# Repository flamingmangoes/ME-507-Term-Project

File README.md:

This project is a 1 rotational degree of freedom prototype for an autonomously controlled momentum exchange device. It includes a reaction flywheel driven by a brushless DC motor, a printed circuit board schematic and layout for the motor controller, and a software architecture to interact with the ESP32 microcontroller.

The hardware consists of a reaction flywheel, its housing, the brushless DC motor, a frictionless air spindle, a test stand, an air compressor, and the PCB with its necessary components. More information can be found in the README.md in the hardware folder: (https://github.com/flamingmangoes/ME-507-Term-Project/blob/main/hardware/README.md)

The software relies on a FreeRTOS-based task architecture, and it has functionality for wireless speed and torque command of the motor, live speed readout, live gain tuning, and downloading a CSV of test data.
The task diagram is as follows: 

The interrupt service handler in the Driver class sends a timestamp to the edge_time queue when it detects a rising edge on the FGOUT pin. The readActual task takes each rising edge and uses the previous rising edge to calculate the electrical frequency of the motor. It then uses that with the direction to calculate the signed speed in RPM, and places that into the speed_actual share. This task runs whenever it detects a value in edge_time, with a latency of 1ms since it uses an ISR.

This share is then read by the webserver task with a period of 10ms, which plots it on a live readout. It is also read by the speedControl task, which then uses the embedded finite state machine (discussed in the next subsection) to decide how to command the motor. It calls the command_speed_PWM method shown earlier to command the motor speed. 

The webserver can command speeds and torques. When a value is input to the form, it places the command in its respective queue. When a speed is commanded, the speedControl task reads it directly. When a torque is commanded, the calcSetpoint task calls the Euler integrator method from the Controller class to convert that into a speed, then sends that to the speedControl task.

The state diagram for the speedControl task is as follows:

The task starts in idle state. Once a value is placed in the speed_cmd queue, the state machine compares the magnitudes and signs of speed_cmd and the current value of speed_actual and decides in what state to place the motor. In the acceleration state, the motor is using its internal control loop to accelerate to the desired speed, then returns to IDLE once it reaches a deadband of 20rpm. In the deceleration state, the BRAKE pin is set to HIGH and the motor decelerates. (Right now, we cannot control the deceleration torque, but we are planning to implement a bang-bang controller to do so). In zero crossing states, once the motor reaches a deadband of 20 rpm around zero, the DIR pin switches polarity and starts accelerating to the desired speed.

When not in IDLE state, the task compares speed_cmd to speed_actual at a period of 10ms. When in IDLE state, the task blocks until another value is placed in the speed_cmd queue. 

Software documentation is included as a Doxygen-generated HTML file structure in the docs folder. The code itself is also well commented and defines all functions, classes, and variables.

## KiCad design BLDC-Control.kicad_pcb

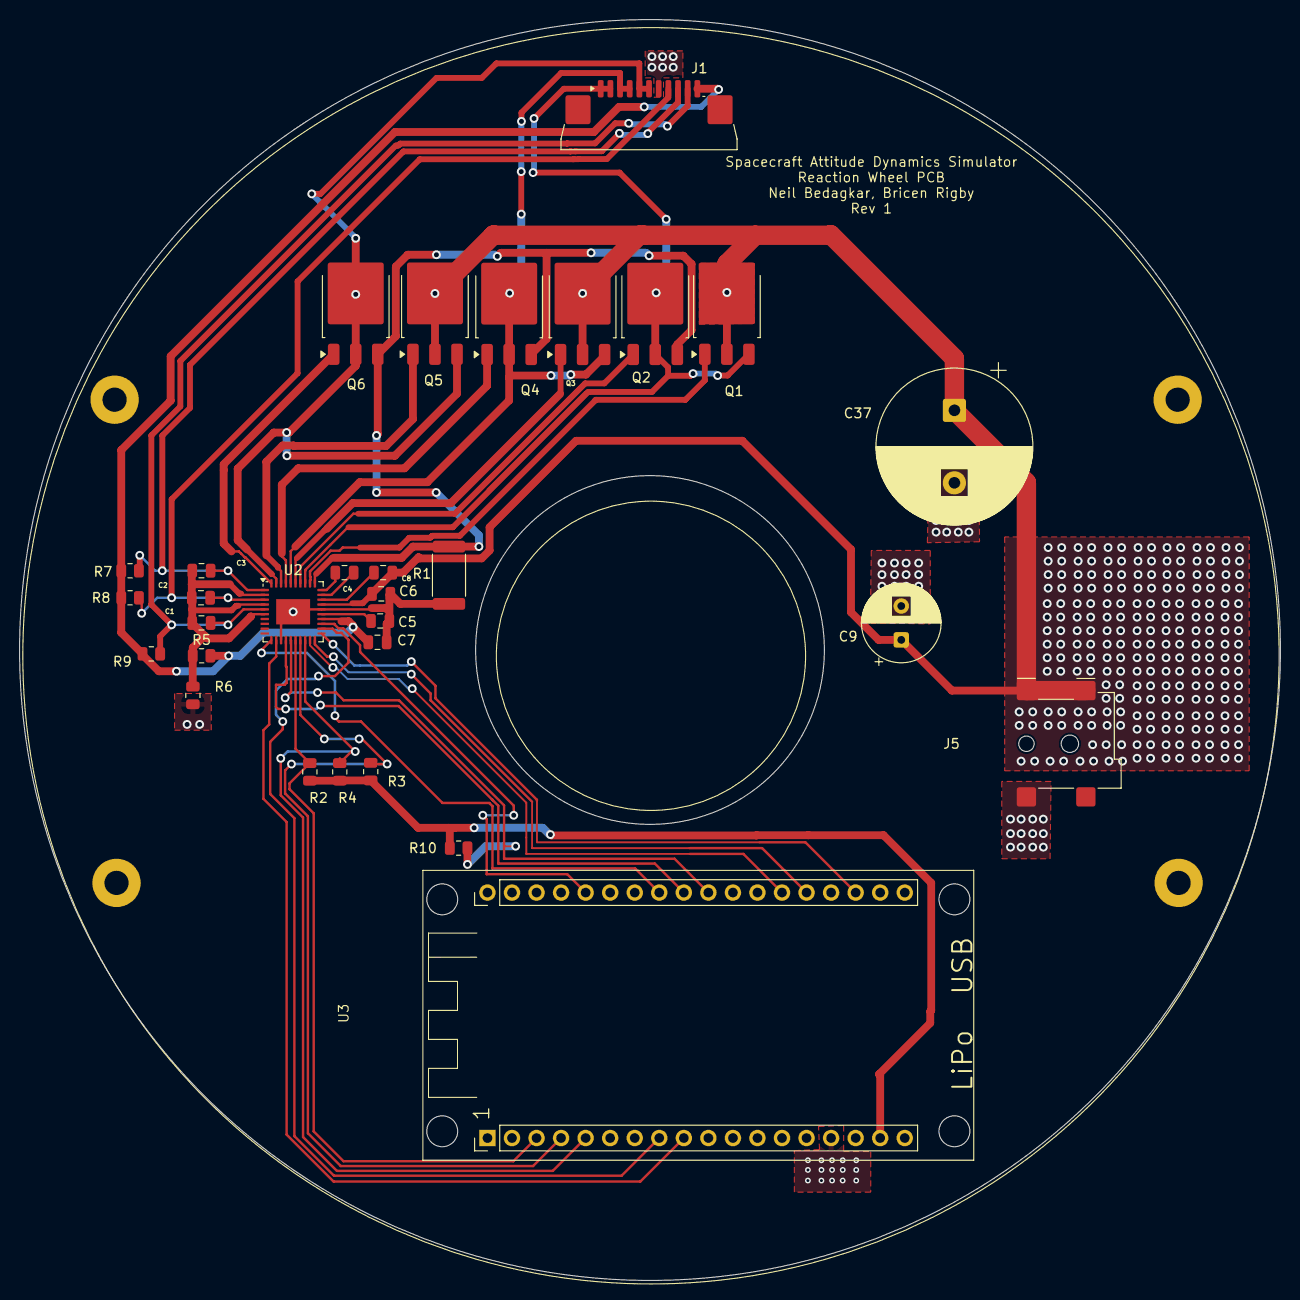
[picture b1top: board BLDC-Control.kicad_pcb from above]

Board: 2 copper layers, 130.5 x 130.5 mm, 34 parts (0 on the bottom side), 34 nets.

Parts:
C1, C2, C3, C4, C6, C7: 0.1 uF; C_0805_2012Metric
C5, C8: 1 uF; C_0805_2012Metric
C9: 47 uF; CP_Radial_D8.0mm_P3.50mm
C37: 470 uF; CP_Radial_D16.0mm_P7.50mm
H1, H2, H3, H4: MountingHole; MountingHole_2.5mm_Pad
J1: BLDC Motor ZIF Connection; JUSHUO_AFA07-S11FCA-00_1x11-1MP_P1.0mm_Horizontal
J5: +24V Power; BarrelJack_Wuerth_694108106102_2.5x5.5mm
Q1, Q2, Q3, Q4, Q5, Q6: Q_NMOS_GDS; TO-252-3_TabPin2
R1: 0.125; R_2512_6332Metric
R2, R3, R4: 10k; R_0805_2012Metric
R5, R6, R7, R8, R9: 2.6k; R_0805_2012Metric
R10: 3.3k; R_0805_2012Metric
U2: DRV8308; Texas_RHA0040E_VQFN-40-1EP_6x6mm_P0.5mm_EP3.52x2.62mm
U3: FireBeetle-ESP32

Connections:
+3V3: R2.2, R3.2, R4.2, R10.1, U3.17 (3V3)
+24V: C6.2, C8.2, C9.1, C37.1, J5.1, Q1.2 (D), Q3.2 (D), Q5.2 (D), U2.27 (VM)
/BRAKE: U2.20 (BRAKE), U3.23 (MCLK/IO12)
/CLKIN: U2.19 (CLKIN), U3.24 (BCLK/IO14)
/DIR: U2.21 (DIR), U3.21 (DI/IO16)
/ENABLE: U2.22 (ENABLE), U3.8 (IO13)
/IOFAULTn_1: R3.1, U2.17 (~FAULTn), U3.4 (IO26)
/IOFGOUT_1: R2.1, U2.16 (FGOUT), U3.3 (IO25)
/IOLOCKn_1: R4.1, U2.18 (~LOCKn), U3.5 (IO27)
/RESET: U2.23 (RESET), U3.32 (IO15)
/SCLK: U2.11 (SCLK), U3.29 (SCK/IO18)
/SCS_1: U2.12 (SCS), U3.9 (IO5)
/SDATAI: U2.14 (SDATAI), U3.28 (MOSI/IO23)
/SDATAO: R10.2, U2.15 (SDATAO), U3.27 (MISO/IO19)
/U: J1.1, J1.2, Q1.3 (S), Q2.2 (D), U2.33 (U)
/UHP: C3.2, J1.9, R7.2, U2.1 (UHP)
/V: J1.3, J1.4, Q3.3 (S), Q4.2 (D), U2.36 (V)
/VHP: C2.2, J1.8, R8.2, U2.3 (VHP)
/VREG: C7.2, J1.11, R5.2, R7.1, R8.1, R9.2, U2.24 (VREG)
/W: J1.5, J1.6, Q5.3 (S), Q6.2 (D), U2.39 (W)
/WHP: C1.2, J1.10, R9.1, U2.5 (WHP)
/xHN: C1.1, C2.1, C3.1, R5.1, R6.2, U2.2 (UHN), U2.4 (VHN), U2.6 (WHN)
GND: C5.1, C6.1, C7.1, C9.2, C37.2, J1.7, J5.2, R1.1, R6.1, U2.13 (SMODE), U2.26 (GND), U2.41 (GND), U3.15 (GND)
unnamed: Q1.1 (G), U2.32 (UHSG)
unnamed: Q2.1 (G), U2.34 (ULSG)
unnamed: Q2.3 (S), Q4.3 (S), Q6.3 (S), R1.2, U2.31 (ISEN)
unnamed: Q3.1 (G), U2.35 (VHSG)
unnamed: Q4.1 (G), U2.37 (VLSG)
unnamed: Q5.1 (G), U2.38 (WHSG)
unnamed: Q6.1 (G), U2.40 (WLSG)
unnamed: C4.2, U2.30 (CP1)
unnamed: C4.1, U2.29 (CP2)
unnamed: C8.1, U2.28 (VCP)
unnamed: C5.2, U2.25 (VINT)

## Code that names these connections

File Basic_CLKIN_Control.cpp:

/** @file bedagkar.cpp
 *  This file contains code used to read the Hall sensor in an ESP32 board and return 
 *  the magnetic field value in mT.
 * @author Neil Bedagkar, with comment format copied from John Ridgely's "pleasedontcrash.cpp"
 *  and calibration assistance from ChatGPT's GPT-5 mini model included in Github Copilot.
 */

#include <Arduino.h>
#include <SPI.h>
#include "PrintStream.h"
SPIClass vspi(VSPI);


// Pin and variable definitions
float freq;
const unsigned long SAMPLE_MS = 100;  // sample window (100 ms)
const int PIN_SCLK  = 18;   // VSPI SCLK
const int PIN_MISO  = 19;   // VSPI MISO  (SDATAO)
const int PIN_MOSI  = 23;   // VSPI MOSI  (SDATAI)
const int PIN_SCS   = 5;    // DRV8308 SCS, ACTIVE HIGH
const int PIN_EN    = 27;    // DRV8308 ENABLE, SET HIGH TO ENABLE
const int PIN_CLKIN = 17;   // DRV8308 CLKIN (from LEDC PWM)
const int PIN_DIR   = 14;   // Optional DIR (set as you like)
const int PIN_FGOUT = 33;    // FGOUT Hall sense output that CLKIN signal matches
const int PIN_FAULTn = 34;   // FAULTn output from DRV8308
const int PIN_LOCKn = 35;   // LOCKn output from DRV8308
const int ledChannel = 0;
const int resolution = 8; // 8-bit resolution


// Helper code for SCS set for communication
inline void scs_begin() 
{ 
  digitalWrite(PIN_SCS, HIGH); 
}

inline void scs_end()   
{ 
  digitalWrite(PIN_SCS, LOW);  
}


// Helper code for ENABLE pin for communication
inline void enable()
{ 
  digitalWrite(PIN_EN, HIGH); 
}

inline void disable()
{ 
  digitalWrite(PIN_EN, LOW); 
}


// Initialize SCS and Enable pins, set SCS and Enable inactive 
void init_pins()
{
  pinMode(PIN_SCS, OUTPUT);
  scs_end(); // SCS inactive
  pinMode(PIN_EN, OUTPUT);
  disable(); // ENABLE inactive
  pinMode(PIN_FGOUT, INPUT);
}


// 24-bit DRV frame to write on MOSI: [R/W:1][Addr:7][Data:16], MSB first
void drv_write(uint8_t addr7, uint16_t data16) 
{
  vspi.beginTransaction(SPISettings(1000000, MSBFIRST, SPI_MODE0)); // 1 MHz, Mode 0
  scs_begin();
  vspi.transfer((0u << 7) | (addr7 & 0x7F));
  vspi.transfer((uint8_t)(data16 >> 8));
  vspi.transfer((uint8_t)(data16 & 0xFF));
  scs_end();
  vspi.endTransaction();
  delayMicroseconds(1); // meet SCS timing
}


// 24-bit DRV frame to read from MISO: [R/W:1][Addr:7][Data:16], MSB first
uint16_t drv_read(uint8_t addr7) 
{
  vspi.beginTransaction(SPISettings(1000000, MSBFIRST, SPI_MODE0));
  scs_begin();
  vspi.transfer((1u << 7) | (addr7 & 0x7F));
  uint8_t msb = vspi.transfer(0x00);
  uint8_t lsb = vspi.transfer(0x00);
  scs_end();
  vspi.endTransaction();
  return (uint16_t(msb) << 8) | lsb;
}


// Build Register 0x00 value: bits [7:6]=PWMF, [5:4]=SPDMODE, [3:2]=FGSEL
// This takes register values that you want to set at the 0x00 address and returns a 16 bit integer that you send to that address
uint16_t reg00_make(uint8_t spdmode, uint8_t pwmf, uint8_t fgsel) {
  return ((uint16_t)(pwmf & 3) << 6) | ((uint16_t)(spdmode & 3) << 4) | ((uint16_t)(fgsel & 3) << 2);
}

// Calculate PWM frequency from desired RPM
float PWM_SETUP(int RPM)
{ 
  // Set up LEDC to output a clock of frequency freq on PIN_CLKIN
  float freq = (RPM / 15); // Calculate frequency in Hz from RPM
  return freq;
}

// Command to set frequency on LEDC channel 0
void COMMAND_FREQ(float freq)
{
  // ledcWriteTone expects an integer frequency (Hz). Cast to uint32_t to be explicit.
  ledcWriteTone(ledChannel, (uint32_t)freq); // automatically outputs on channel 0 (PIN_CLKIN as configured above) at a 50% duty cycle
}


// Read FGOUT pin and compute frequency and RPM every SAMPLE_MS milliseconds
void readAndPrintRPM() 
{
  static int lastState = LOW;
  static unsigned long edgeCount = 0;
  static unsigned long lastSample = millis();

  // 1. Detect rising edges
  int currentState = digitalRead(PIN_FGOUT);
  if (currentState == HIGH && lastState == LOW) {
    edgeCount++;
  }
  lastState = currentState;

  // 2. Every SAMPLE_MS, compute and print frequency/RPM
  unsigned long now = millis();
  if (now - lastSample >= SAMPLE_MS) {
    float dt = (now - lastSample) / 1000.0;  // seconds
    lastSample = now;

    float freq = edgeCount / dt;             // Hz
    float rpm  = (15 * freq);    // mechanical RPM
    Serial.printf("FGOUT freq = %.1f Hz,  RPM = %.1f\n", freq, rpm);

    edgeCount = 0;  // reset count for next window
  }
}


void setup() 
{
  Serial.begin(115200);
  delay(10000); // 10 secs for the user to open Serial Monitor!
  Serial << "Hello! This begins the serial reader." << endl;
  vspi.begin(PIN_SCLK, PIN_MISO, PIN_MOSI, -1); 
  init_pins();

  // Program SPDMODE=00 (Clock Frequency), PWMF=01 (~50kHz), FGSEL=00 (Hall-U)
  uint16_t r00 = reg00_make(/*spdmode=*/0b00, /*pwmf=*/0b01, /*fgsel=*/0b00);
  drv_write(0x00, r00);

  enable(); // Enable the DRV8308
  delay(2); // Wait for DRV8308 to power up

  // Configure LEDC: compute frequency, setup channel, attach pin, then start tone
  freq = PWM_SETUP(150);
  ledcSetup(ledChannel, (uint32_t)freq, resolution); // configure timer for the channel
  ledcAttachPin(PIN_CLKIN, ledChannel);
  COMMAND_FREQ(freq);

}

void loop() 
{
  readAndPrintRPM();
  delay(10);
}

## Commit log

2025-10-17 Add files via upload
    1 microcontroller 1 motor driver
2025-10-17 Add files via upload
    changed SDATAI label on MCU to SDATAO to reflect MOSI pin
2025-10-29 Add files via upload
    Code for basic control of DRV8308 via CLKIN frequency mode
2025-11-14 Adding final board design
    schematic and pcb design
2025-11-20 Add files via upload
    WIP for coding architrecture
2025-12-02 Add files via upload
    to begin wifi network:
    uncomment setup_wifi() and xTaskCreate for webserver in setup()
    connect to network with project name and password defined in if statement at the beginning
    go to http://192.168.5.1
2025-12-03 Add files via upload
    pre-network
2025-12-04 Add files via upload
    +improved GUI with gain and speed control (do not let the name deceive you)
    +tuning
    --> high COMPK1 = good steady state, low COMPK1 = good transient response
    100 seems to be a good balance
    tuned values are loaded as defaults; FILK1/FILK2/COMPK1/COMPK2 have the heaviest impact on performance, would mess with those mostly if retuning
2025-12-09 Final Architecture
2025-12-09 Second Version of the BLDC PCB
    Includes proper ZIF connector and removes unnecessary vias.
2025-12-09 Final BLDC Control PCB Design
2025-12-09 Uploaded 3D models
2025-12-09 more 3d models
2025-12-10 Added capability for downloading CSV
2025-12-10 Create RWcad
2025-12-10 Caleb Nalley's Reaction Wheel + Motor CAD
2025-12-10 Doxygen-generated documentation
2025-12-10 Create adsf
2025-12-10 Motor and motor driver datasheets
